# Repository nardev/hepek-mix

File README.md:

#Hepek Android

It's just a test app, real one under the development

note: define MQTT_USERNAME and MQTT_PASSWORD environment variables prior to building the app

#Hepek Arduino

1. Convert desired wav audio to c header file with this https://github.com/olleolleolle/wav2c
note: have in mind that you have very little space on ATmega328P microcontroller chip
2. Build and upload the scatch
3. Hook the speaker, button and RGB led or use Hepek Shield

#Hepek Arduino Shield

This was just a test of OSH Park service, works but doesn't have audio amplifier
You can order one here: https://oshpark.com/shared_projects/xxv7qtNv

#rc sockets

You need RC Sockets and RC 433MHz transmitter/receiver for this.

Also, get some libs
mosquitto cpp: http://www.kevinboone.net/mosquitto-test.html
rc-switch: https://github.com/sui77/rc-switch
yaml-cpp: https://github.com/jbeder/yaml-cpp

1. Read RC codes fromremote controller
2. Edit .yaml config  file
3. Build the app
4. Set the app to run as a service in rpi

Any issues or questons, ask me at vedran at nardev dot org

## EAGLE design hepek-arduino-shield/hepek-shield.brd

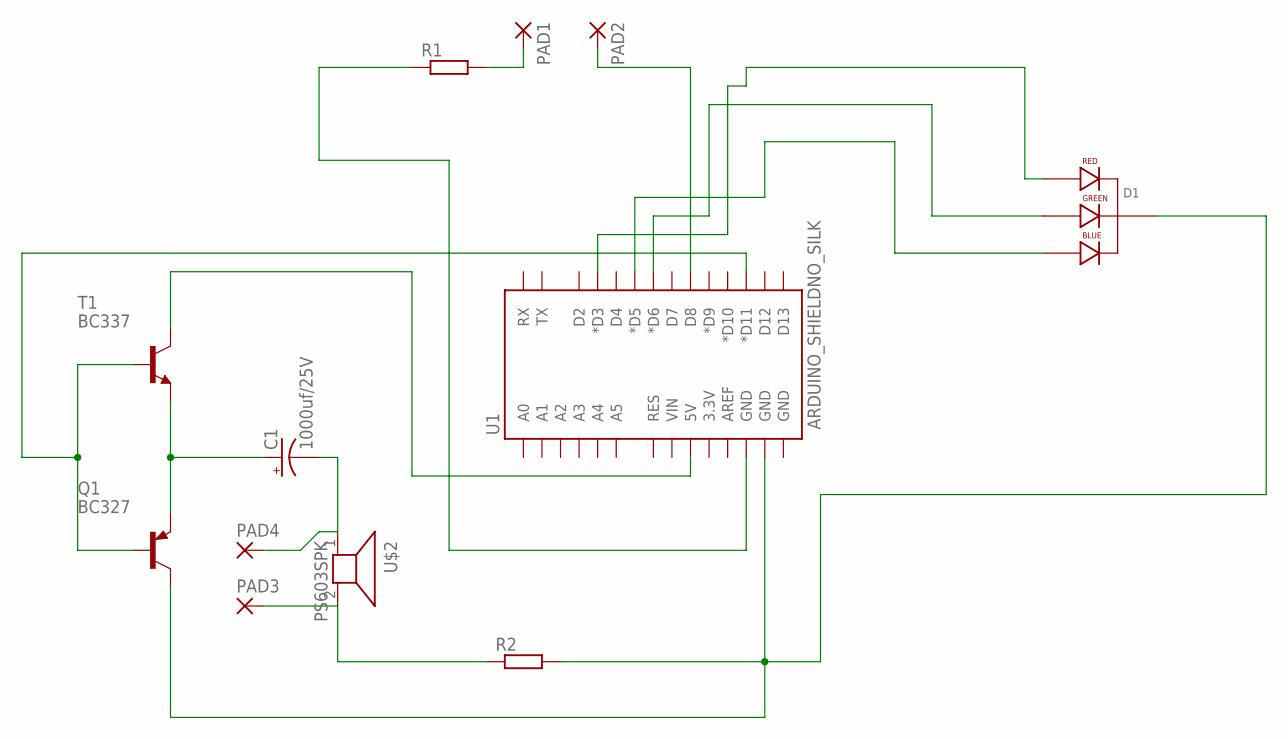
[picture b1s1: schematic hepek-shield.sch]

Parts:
C1: 1000uf/25V; CPOL-RADIAL-1000UF-25V-KIT
D1: LED-RGB-CC-THRUCLEAR; LED-RGB-THRU
PAD1, PAD2, PAD3, PAD4: 2,15/1,0
Q1: BC327; TO92-EBC
R1, R2: R-EU_0204/7; 0204/7
T1: BC337; TO92
U1: ARDUINO_SHIELDNO_SILK; DUEMILANOVE_VIAS
U$2: PS603SPK; PS603

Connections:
unnamed: D1.1 (RED_CATHODE), U1.D3 (*D3)
unnamed: D1.4 (BLUE_CATHODE), U1.D5 (*D5)
unnamed: D1.3 (GREEN_CATHODE), U1.D6 (*D6)
unnamed: PAD1.1, R1.2
unnamed: PAD2.1, U1.D8
unnamed: T1.3 (C), U1.5V
unnamed: PAD3.1, R2.1, U$2.2
unnamed: C1.+, Q1.E, T1.1 (E)
unnamed: C1.-, PAD4.1, U$2.1
unnamed: D1.2 (CATHODE), Q1.C, R2.2, U1.GND@1 (GND)
unnamed: Q1.B, T1.2 (B), U1.D11 (*D11)
unnamed: R1.1, U1.GND@2 (GND)

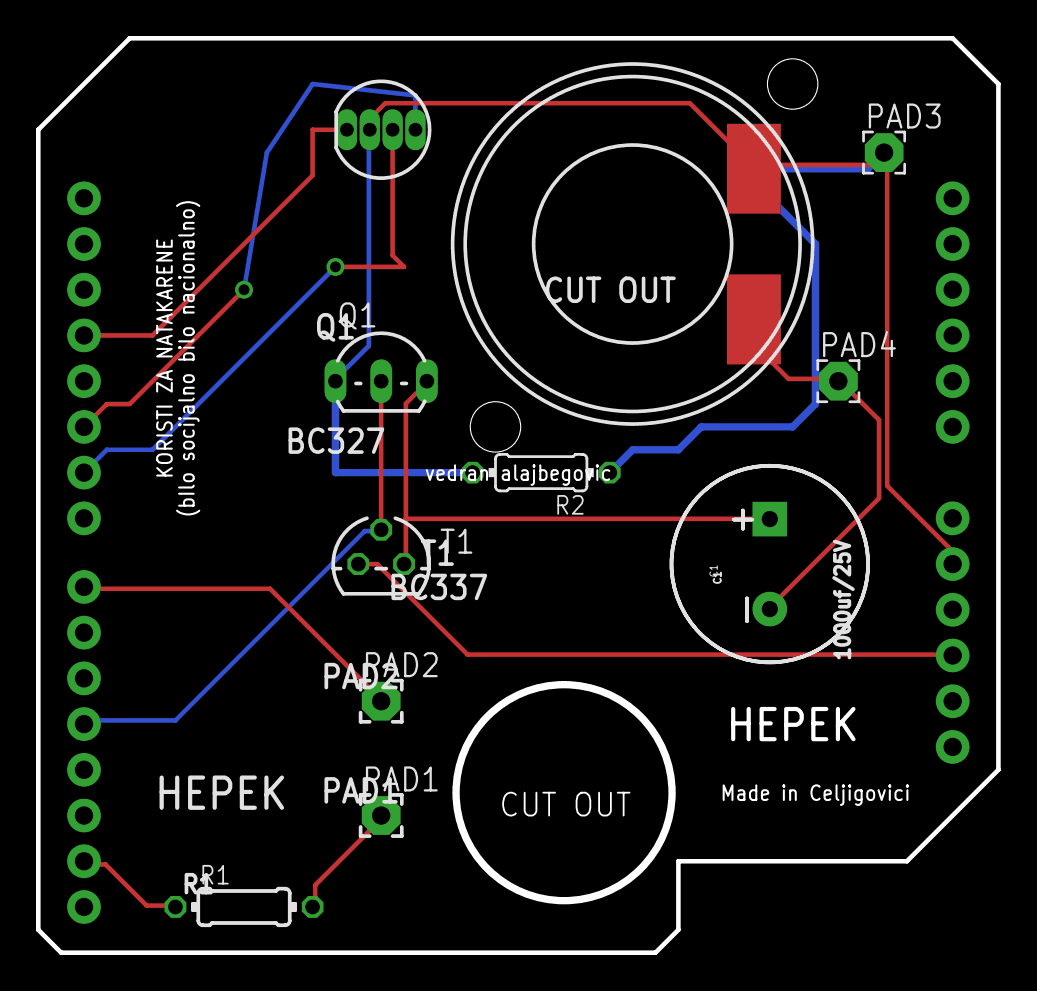
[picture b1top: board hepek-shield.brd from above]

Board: 2 copper layers, 53.2 x 50.6 mm, 12 parts (0 on the bottom side), 12 nets.

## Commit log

2017-05-23 git mix all init

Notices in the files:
parts and their libraries:
SparkFun-Capacitors: Licensing: Creative Commons ShareAlike 4.0 International - https://creativecommons.org/licenses/by-sa/4.0
